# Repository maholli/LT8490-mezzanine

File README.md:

# LT8490-mezzanine
Castellated mezzanine board for LT8490 solar charging buck/boost charger

Modular solar energy harvester and battery charger
- High power (>600W)
- Vsolar input: ~5V to 80V
- Vbatt 1.3V to 80V (covers everything from 1S, 2S, ... 20S, etc)
- Max power point tracking (MPPT "perturb and observe")
- Buck-Boost design (solar voltage can be below or above battery voltage)
  - Switching freq: 100 to 400kHz
  - Efficiency ~90% or better. Depends on inductor choice
- Can be connected in parallel (one on each face, for example), optional clock sync for max parallel efficiency
- Radiation tolerant module design:
  1. LT8490/LT8491 (charging IC) -- SEE: no destructive, SEL LET TH 42.2 MeV-cm2/mg at 85C, TID: N/A (Allen 10.1109/NSREC.2017.8115429)
  2. Si7106DN (power FETs)-- SEE: no destructive up to 1E11 n/cm2, no SET or SEL up to LET 58 MeV-cm2/mg 25C, TID: >10krad 25C VDS=5V (Fairbanks 10.1109/REDW.2013.6658191)
  3. BSS84/MBT2222ADW1T1 -- refer to PyCubed documentation
- (Optional) I2C telemetry: Vbat (10mV res), Vin (10mV res), Iin (1mA res), Iout (1mA res), efficiency, etc...

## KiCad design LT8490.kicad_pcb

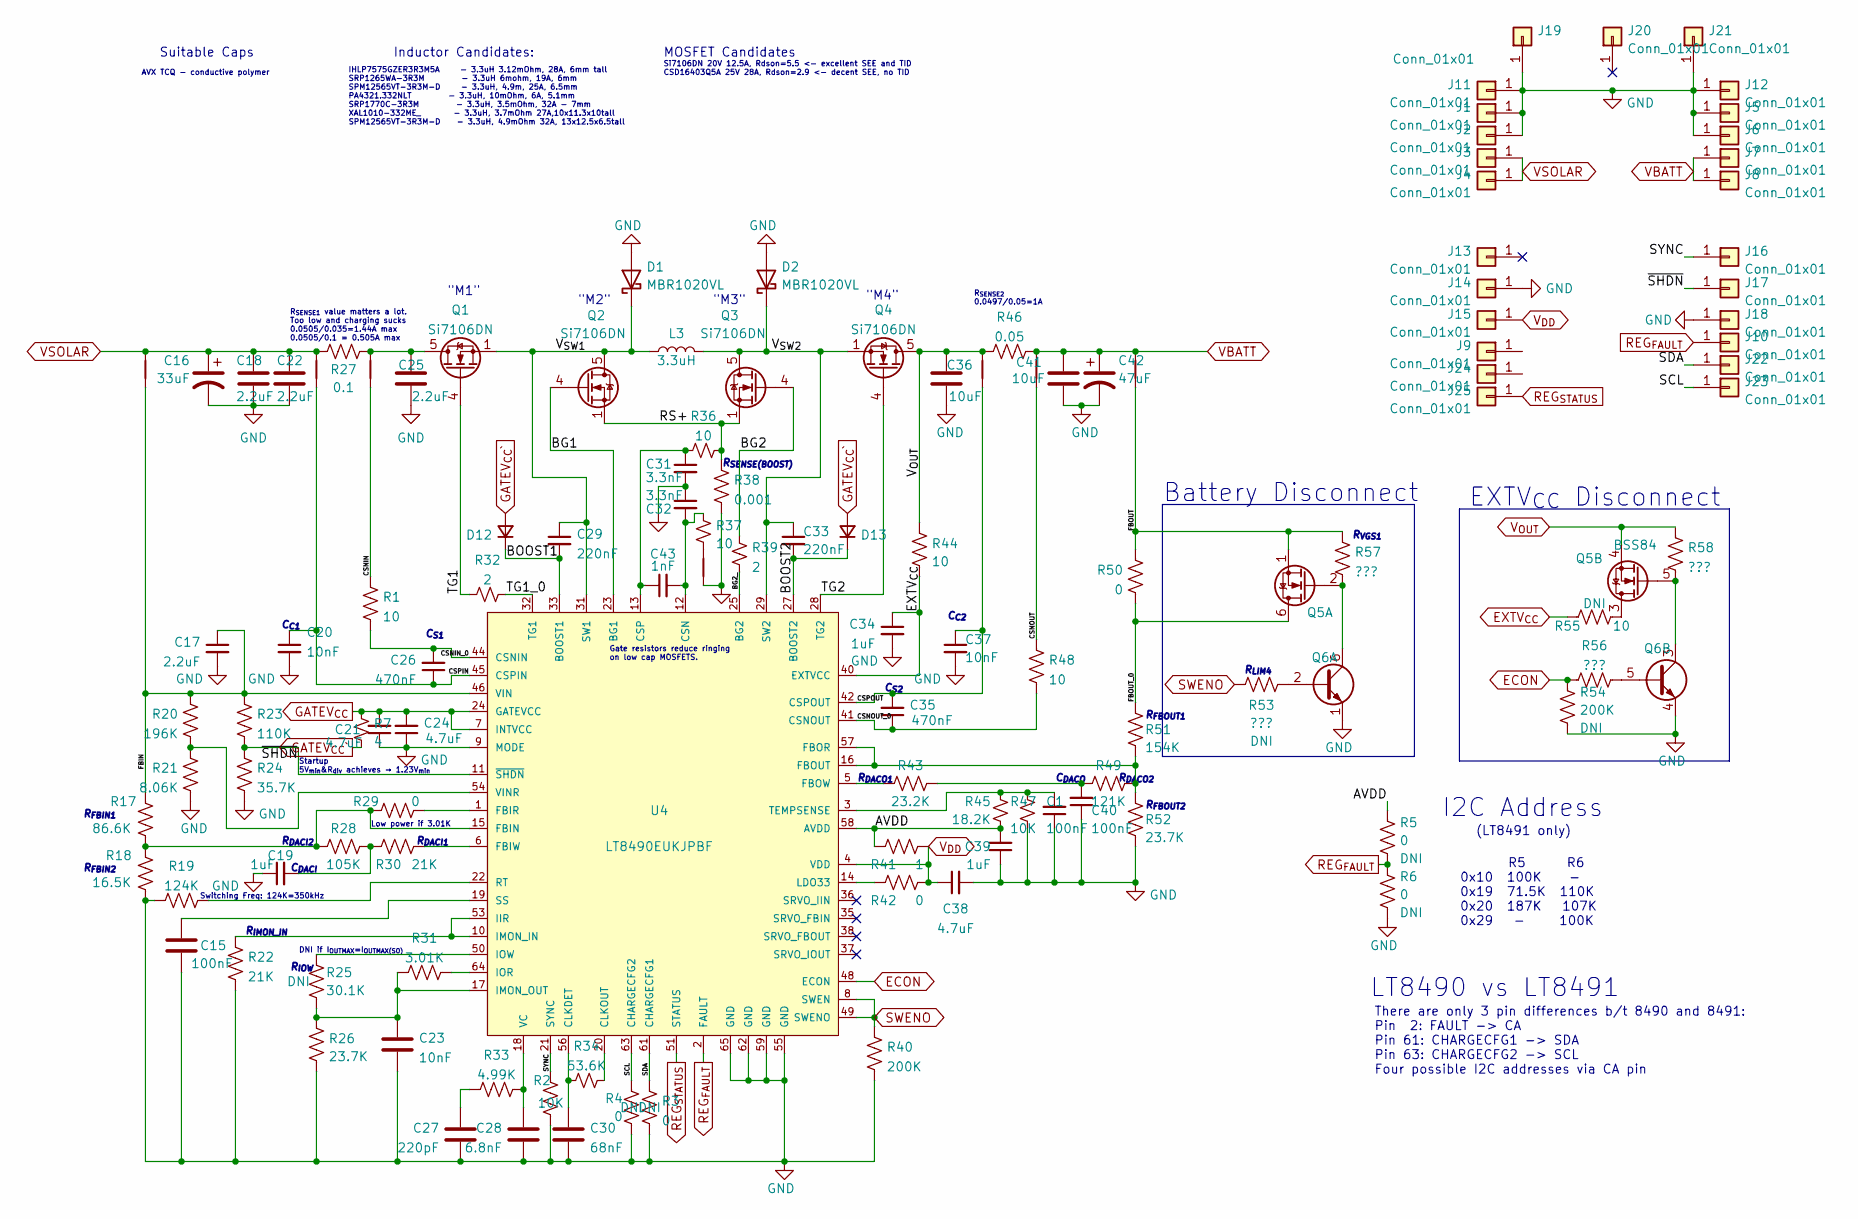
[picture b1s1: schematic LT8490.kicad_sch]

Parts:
C1, C15, C40: 100nF; C_0603_1608Metric
C16: 33uF; CP_EIA-7343-30_AVX-N; Voltage 16V; Manufacturer_Part_Number TCQD336M016R0070E
C17: 2.2uF; C_0603_1608Metric
C18, C22, C25: 2.2uF; C_0805_2012Metric
C19, C34, C39: 1uF; C_0603_1608Metric
C20, C23, C37: 10nF; C_0603_1608Metric
C21, C24, C38: 4.7uF; C_0603_1608Metric
C26, C35: 470nF; C_0603_1608Metric
C27: 220pF; C_0603_1608Metric
C28: 6.8nF; C_0603_1608Metric
C29, C33: 220nF; C_0603_1608Metric
C30: 68nF; C_0603_1608Metric
C31, C32: 3.3nF; C_0603_1608Metric
C36, C41: 10uF; C_0805_2012Metric
C42: 47uF; CP_EIA-7343-30_AVX-N; Voltage 16V; Manufacturer_Part_Number TCQD476M016R0070E
C43: 1nF; C_0603_1608Metric
D1, D2: MBR1020VL; D_SOD-123F
D12, D13: CMMR1U-02 TR; D_SOD-123F
J1, J2, J3, J4, J5, J6, J7, J8, J9, J10, J11, J12, J13, J14, J15, J16, J17, J18, J19, J20, J21, J22, J23, J24, J25: Conn_01x01; castellated_05mm
L3: 3.3uH; L_SRP1770C
NT1, NT2, NT3, NT4, NT5, NT6, NT7: NetTie_2; NetTie-2_SMD_Pad0.5mm
Q1, Q2, Q3, Q4: Si7106DN; SIS862DNT1GE3; Manufacturer_Part_Number Si7106DN
Q5: BSS84; BSS138DWQ-7
Q6: MBT2222ADW1T1; SOT-363_SC-70-6; Manufacturer_Part_Number MBT2222ADW1T1
R1, R36, R37, R44, R48, R55: 10; R_0603_1608Metric
R2, R47: 10K; R_0603_1608Metric
R3, R4, R29, R42, R50: 0; R_0603_1608Metric
R5, R6: 0; R_0402_1005Metric
R7: 4; R_0603_1608Metric
R17: 86.6K; R_0603_1608Metric
R18: 16.5K; R_0603_1608Metric
R19: 124K; R_0603_1608Metric
R20: 196K; R_0603_1608Metric
R21: 8.06K; R_0603_1608Metric
R22, R30: 21K; R_0603_1608Metric
R23: 110K; R_0603_1608Metric
R24: 35.7K; R_0603_1608Metric
R25: 30.1K; R_0603_1608Metric
R26, R52: 23.7K; R_0603_1608Metric
R27: 0.1; R_1206_3216Metric
R28: 105K; R_0603_1608Metric
R31: 3.01K; R_0603_1608Metric
R32, R39: 2; R_0603_1608Metric
R33: 4.99K; R_0603_1608Metric
R34: 53.6K; R_0603_1608Metric
R38: 0.001; R_1206_3216Metric
R40, R54: 200K; R_0603_1608Metric
R41: 1; R_0603_1608Metric
R43: 23.2K; R_0603_1608Metric
R45: 18.2K; R_0603_1608Metric
R46: 0.05; R_1206_3216Metric
R49: 121K; R_0603_1608Metric
R51: 154K; R_0603_1608Metric
R53, R56, R57, R58: ???; R_0603_1608Metric
U4: LT8490EUKJPBF; LT8490EUKJ#PBF

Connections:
/AVDD: C39.2, R5.1, R41.2, R45.2, U4.58 (AVDD)
/BG1: Q2.4 (G), U4.23 (BG1)
/BG2: Q3.4 (G), R39.1
/BG2_: R39.2, U4.25 (BG2)
/BOOST1: C29.2, D12.1 (K), U4.33 (BOOST1)
/BOOST2: C33.2, D13.1 (K), U4.27 (BOOST2)
/CSNIN: NT3.1, R1.1
/CSNIN_0: C26.2, R1.2, U4.44 (CSNIN)
/CSNOUT: NT5.1, R48.1
/CSNOUT_0: C35.1, R48.2, U4.41 (CSNOUT)
/CSPIN: C20.1, C26.1, NT2.1, U4.45 (CSPIN)
/CSPOUT: C35.2, C37.1, NT4.1, U4.42 (CSPOUT)
/FBIN: C17.1, NT6.1, R17.1, R20.1, R23.1, U4.46 (VIN)
/FBOUT: NT7.1, Q5.1 (S2), R50.1, R57.2
/FBOUT_0: Q5.6 (D1), R50.2, R51.1
/RS+: Q2.1 (S), Q2.2 (S), Q2.3 (S), Q3.1 (S), Q3.2 (S), Q3.3 (S), R36.1, R38.1
/SCL: J23.1, R4.1, U4.63 (CHARGECFG2)
/SDA: J22.1, R3.1, U4.61 (CHARGECFG1)
/SYNC: J16.1, R2.1, U4.21 (SYNC)
/TG1: Q1.4 (G), R32.2
/TG1_0: R32.1, U4.32 (TG1)
/TG2: Q4.4 (G), U4.28 (TG2)
/V_{SW1}: C29.1, D1.1 (K), L3.1, Q1.1 (S), Q1.2 (S), Q1.3 (S), Q2.5 (D), U4.31 (SW1)
/V_{SW2}: C33.1, D2.1 (K), L3.2, Q3.5 (D), Q4.1 (S), Q4.2 (S), Q4.3 (S), U4.29 (SW2)
/~SHDN: J17.1, R23.2, R24.1, U4.11 (~SHDN)
ECON: R54.1, R56.1, U4.48 (ECON)
EXTV_{CC}: C34.1, R44.2, R55.2, U4.40 (EXTVCC)
GATEV_{CC}: C21.2, C24.2, R7.2, U4.7 (INTVCC), U4.24 (GATEVCC)
GATEV_{CC}`: D12.2 (A), D13.2 (A), R7.1
GND: C1.1, C15.2, C16.2, C17.2, C18.2, C19.1, C20.2, C21.1, C22.2, C23.2, C24.1, C25.2, C27.2, C28.1, C30.2, C31.2, C32.1, C34.2, C36.2, C37.2, C38.2, C39.1, C40.1, C41.2, C42.2, D1.2 (A), D2.2 (A), J1.1, J2.1, J5.1, J6.1, J11.1, J12.1, J14.1, J18.1, J19.1, J21.1, NT1.1, Q6.1 (E1), Q6.4 (E2), R2.2, R3.2, R4.2, R6.2, R18.2, R19.2, R21.2, R22.2, R24.2, R26.2, R38.2, R40.2, R47.1, R52.2, R54.2, U4.9 (MODE), U4.55 (GND), U4.59 (GND), U4.62 (GND), U4.65 (GND)
unnamed: C1.2, R45.1, R47.2, U4.3 (TEMPSENSE)
unnamed: C15.1, U4.19 (SS)
unnamed: C19.2, R28.1, R30.2
unnamed: C23.1, R25.2, R26.1, R31.2, U4.17 (IMON_OUT)
unnamed: C25.1, NT3.2, Q1.5 (D), R27.2
unnamed: C27.1, R33.1
unnamed: C28.2, R33.2, U4.18 (VC)
unnamed: C30.1, R34.1, U4.56 (CLKDET)
unnamed: C31.1, C43.1, R36.2, U4.13 (CSP)
unnamed: C32.2, C43.2, R37.1, U4.12 (CSN)
unnamed: C40.2, R43.1, R49.2
unnamed: NT1.2, R37.2
unnamed: Q5.2 (G2), Q6.6 (C1), R57.1
unnamed: Q5.3 (D2), R55.1
unnamed: Q5.5 (G1), Q6.3 (C2), R58.1
unnamed: Q6.2 (B1), R53.2
unnamed: Q6.5 (B2), R56.2
unnamed: R17.2, R18.1, R28.2, R29.2, U4.15 (FBIN)
unnamed: R19.1, U4.22 (RT)
unnamed: R20.2, R21.1, U4.54 (VINR)
unnamed: R22.1, U4.10 (IMON_IN), U4.53 (IIR)
unnamed: R25.1, U4.50 (IOW)
unnamed: R29.1, U4.1 (FBIR)
unnamed: R30.1, U4.6 (FBIW)
unnamed: R31.1, U4.64 (IOR)
unnamed: R34.2, U4.20 (CLKOUT)
unnamed: R42.2, U4.14 (LDO33)
unnamed: R43.2, U4.5 (FBOW)
unnamed: R49.1, R51.2, R52.1, U4.16 (FBOUT), U4.57 (FBOR)
REG_{FAULT}: J10.1, R5.2, R6.1, U4.2 (FAULT)
REG_{STATUS}: J25.1, U4.51 (STATUS)
SWENO: R40.1, R53.1, U4.8 (SWEN), U4.49 (SWENO)
VBATT: C41.1, C42.1, J7.1, J8.1, NT5.2, NT7.2, R46.2
VSOLAR: C16.1, C18.1, C22.1, J3.1, J4.1, NT2.2, NT6.2, R27.1
V_{DD}: C38.1, J15.1, R41.1, R42.1, U4.4 (VDD)
V_{OUT}: C36.1, NT4.2, Q4.5 (D), Q5.4 (S1), R44.1, R46.1, R58.2

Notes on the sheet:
R_{DACI1}
C_{DACO}
C_{C2}
DNI if I_{OUTMAX}=I_{OUTMAX(SO)}
Battery Disconnect
R_{IMON_IN}
Startup 5V_{min}&R_{div} achieves → 1.23V_{min}
C_{S1}
C_{S2}
Switching Freq: 124K=350kHz
Suitable Caps
R_{LIM4}
"M4"
Gate resistors reduce ringing on low cap MOSFETS.
R_{DACO2}
Si7106DN 20V 12.5A, Rdson=5.5 <- excellent SEE and TID CSD16403Q5A 25V 28A, Rdson=2.9 <- decent SEE, no TID
There are only 3 pin differences b/t 8490 and 8491: Pin 2: FAULT -> CA Pin 61: CHARGECFG1 -> SDA Pin 63: CHARGECFG2 -> SCL Four possible I2C addresses via CA pin
R_{DACI2}
R_{SENSE(BOOST)}
R_{FBIN2}
C_{C1}
R_{DACO1}
R5 R6 0x10 100K - 0x19 71.5K 110K 0x20 187K 107K 0x29 - 100K
IHLP7575GZER3R3M5A - 3.3uH 3.12mOhm, 28A, 6mm tall SRP1265WA-3R3M - 3.3uH 6mohm, 19A, 6mm SPM12565VT-3R3M-D - 3.3uH, 4.9m, 25A, 6.5mm PA4321.332NLT - 3.3uH, 10mOhm, 6A, 5.1mm SRP1770C-3R3M - 3.3uH, 3.5mOhm, 32A - 7mm XAL1010-332ME_ - 3.3uH, 3.7mOhm 27A,10x11.3x10tall SPM12565VT-3R3M-D - 3.3uH, 4.9m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
R_{SENSE1} value matters a lot. Too low and charging sucks 0.0505/0.035=1.44A max 0.0505/0.1 = 0.505A max
EXTV_{CC} Disconnect
"M2"
"M3"
R_{FBIN1}
R_{IOW}
(LT8491 only)
MOSFET Candidates
AVX TCQ - conductive polymer
C_{DACI}
"M1"
R_{FBOUT2}
Inductor Candidates:
R_{FBOUT1}
R_{SENSE2} 0.0497/0.05=1A
LT8490 vs LT8491

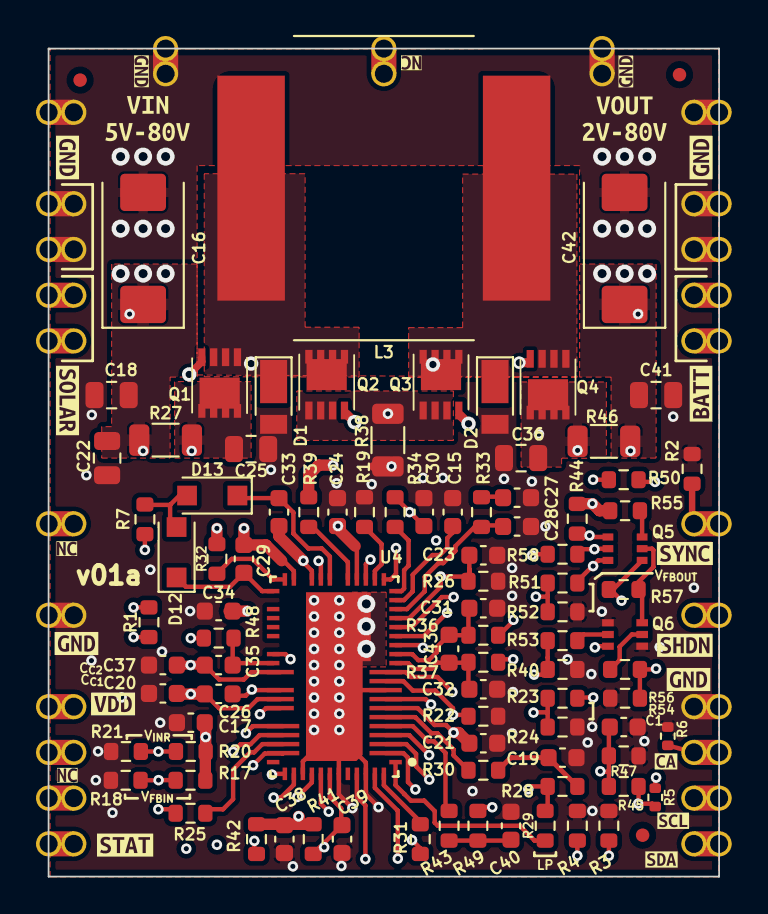
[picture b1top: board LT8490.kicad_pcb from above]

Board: 6 copper layers, 37.2 x 46.0 mm, 145 parts (0 on the bottom side), 66 nets.

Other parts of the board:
Ref**: Val**; holliday
kibuzzard-62D49DAC, kibuzzard-62D49DAC#2, kibuzzard-62D49DAC#3: G***; kibuzzard-62D49DAC
kibuzzard-62D49DF0, kibuzzard-62D49DF0#2: G***; kibuzzard-62D49DF0
kibuzzard-623CC1D5, kibuzzard-623CC1D5#2, kibuzzard-623CC1D5#3, kibuzzard-623CC1D5#4: G***; kibuzzard-623CC1D5
kibuzzard-623CC1F4: G***; kibuzzard-623CC1F4
kibuzzard-623CC3F2: G***; kibuzzard-623CC3F2
kibuzzard-623CC9B2: G***; kibuzzard-623CC9B2
kibuzzard-623CC23C: G***; kibuzzard-623CC23C
kibuzzard-623CCAD0: G***; kibuzzard-623CCAD0
kibuzzard-623CCAFA: G***; kibuzzard-623CCAFA
kibuzzard-623CCB0B: G***; kibuzzard-623CCB0B
kibuzzard-623CCB15: G***; kibuzzard-623CCB15
kibuzzard-623CCD34: G***; kibuzzard-623CCD34
kibuzzard-623DE3C4: G***; kibuzzard-623DE3C4
kibuzzard-623E06E1: G***; kibuzzard-623E06E1
kibuzzard-623E06ED: G***; kibuzzard-623E06ED
kibuzzard-623E06FB: G***; kibuzzard-623E06FB

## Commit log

2022-03-21 inital commit -- schematic & layout unfinished
2022-03-21 routed on 6 layers. Possible to do 4?
2022-03-23 evaluating layout for sensitive signals
2022-03-24 cleaned up routing
2022-03-24 passed DRC & extra SS labeling
2022-03-29 Added LT8491 functionality (I2C)
2022-04-21 Added module highlights and part justifications to readme
2022-04-21 more highlights
2022-04-21 readme
2022-05-13 update gitignore
2022-05-13 pin labels for schematic and layout blocks
2022-07-03 shift big caps 2mm
2022-07-03 proper step file
2022-07-12 plane cleanup
2022-07-12 added i2c address resistors to CA
2022-07-17 cleanup before fab
2022-07-17 changed some silkscreen
2022-07-20 gerbers
2022-08-06 start of v05d-specific changes
2022-08-06 Revert "start of v05d-specific changes"
    This reverts commit 6ad8f1aa8d777c3cbccc6a24b8135bcf496e0b3b.
2022-12-11 tweaks after v00 build
2022-12-14 tweaking performance
2022-12-31 minor tweaks after bench testing
2023-01-09 beefed up LDO3V3
2024-05-19 fix unnecessarily tight via-to-pad tolerance in one area
